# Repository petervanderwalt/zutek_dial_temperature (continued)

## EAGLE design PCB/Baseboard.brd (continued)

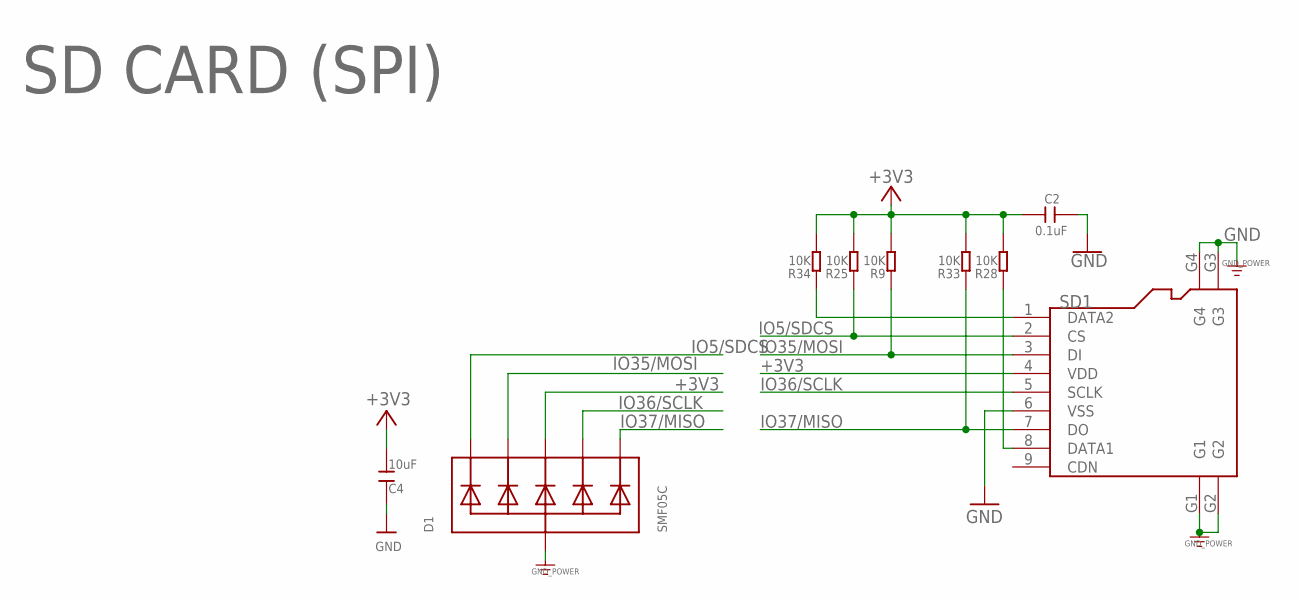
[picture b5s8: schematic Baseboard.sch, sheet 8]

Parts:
C2: 0.1uF; DISCRETE_C0603
C4: 10uF; DISCRETE_C1206
D1: SMF05C; SOT363
R9, R25, R28, R33, R34: 10K; DISCRETE_R0603
SD1: HOLDER-MICROSD-9P; 9P-SMD-W/-RING

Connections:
+3V3: C2.2, C4.2, D1.4 (C3), R9.2, R25.2, R28.2, R33.2, R34.2, SD1.4 (VDD); also elsewhere on the board
GND: C2.1, C4.1, D1.2 (A), SD1.6 (VSS), SD1.G1, SD1.G2, SD1.G3, SD1.G4; also elsewhere on the board
IO5/SDCS: D1.1 (C1), R25.1, SD1.2 (CS); also elsewhere on the board
IO35/MOSI: D1.3 (C2), R9.1, SD1.3 (DI); also elsewhere on the board
IO36/SCLK: D1.5 (C4), SD1.5 (SCLK); also elsewhere on the board
IO37/MISO: D1.6 (C5), R33.1, SD1.7 (DO); also elsewhere on the board
unnamed: R34.1, SD1.1 (DATA2)
unnamed: R28.1, SD1.8 (DATA1)

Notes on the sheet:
SD CARD (SPI)

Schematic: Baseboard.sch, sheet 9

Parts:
C28, C29: 22P; C0603
C30, C31, C34: 0.1uF; C0603
C32, C35: 10uF; C1206
C33: 0.47uF; C0603
IC2: CH376; CH376S-SOIC
R46, R61: 100K; R0603
USB1: USB-A-H
XTAL2: 12MHz; CRYSTAL_3.2X2.5

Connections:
+3V3: C30.2, C33.1, C34.1, C35.1, IC2.PCS#, IC2.V3, IC2.VCC, R46.2, R61.2; also elsewhere on the board
+5V: C31.2, C32.2, USB1.VBUS; also elsewhere on the board
GND: C28.2, C29.2, C30.1, C31.1, C32.1, C34.2, C35.2, IC2.GND, IC2.RD#, IC2.WR#, USB1.GND; also elsewhere on the board
IO35/MOSI: IC2.SDI/D6; also elsewhere on the board
IO36/SCLK: IC2.SCK/D5; also elsewhere on the board
IO37/MISO: IC2.SDO/D7; also elsewhere on the board
unnamed: IC2.UD+, USB1.D+
unnamed: IC2.UD-, USB1.D-
unnamed: C28.1, IC2.XI, XTAL2.1
unnamed: C29.1, IC2.XO, XTAL2.2
unnamed: IC2.TXD, R46.1
RESET_IN: C33.2, IC2.RSTI
RESET_OUT: IC2.SD-DO
SPI_BUSY: IC2.BZ/D4
USBMS_CS: IC2.SCS/D3, R61.1; also elsewhere on the board
USB_INT: IC2.INT#; also elsewhere on the board

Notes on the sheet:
USB MASS STORAGE (SPI)

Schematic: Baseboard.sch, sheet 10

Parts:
D2_M1, D2_M2, D2_M3, D2_M4, D2_M5, D2_M6, D2_M7, D2_M8: GRN; CHIP-LED0603
D30_RL1, D30_RL2, D30_RL3, D30_RL4, D30_RL5, D30_RL6, D30_RL7, D30_RL8: B5819W; SOD123FL
F1_RL1, F1_RL2, F1_RL3, F1_RL4, F1_RL5, F1_RL6, F1_RL7, F1_RL8: 24V 460mA; 1206L
IC7: PCF8574T; SO16W
MOSFET1, MOSFET2, MOSFET3, MOSFET4, MOSFET5, MOSFET6, MOSFET7, MOSFET8: WJ212R-THR-3.5-2
Q2_RL1, Q2_RL2, Q2_RL3, Q2_RL4, Q2_RL5, Q2_RL6, Q2_RL7, Q2_RL8: ST3422A; SOT-23
R1, R3, R6, R62, R84, R85, R86, R87, R88, R90, R92, R94, R100, R101, R102, R103: 1K; R0603
R2, R4, R8, R63, R89, R91, R93, R95: 100K; R0603
R47, R48, R49, R50, R82, R83, R96, R97, R98, R99: 10K; R0603
SJ8, SJ9, SJ10: SJ

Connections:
+3V3: IC7.16 (VDD), R82.2, R83.2, R84.1, R85.1, R86.1, R87.1, R100.1, R101.1, R102.1, R103.1; also elsewhere on the board
+24V: D30_RL1.C, D30_RL2.C, D30_RL3.C, D30_RL4.C, D30_RL5.C, D30_RL6.C, D30_RL7.C, D30_RL8.C, F1_RL1.2, F1_RL2.2, F1_RL3.2, F1_RL4.2, F1_RL5.2, F1_RL6.2, F1_RL7.2, F1_RL8.2, R47.1, R48.1, R49.1, R50.1, R96.1, R97.1, R98.1, R99.1; also elsewhere on the board
GND: IC7.8 (VSS), Q2_RL1.P2 (S), Q2_RL2.P2 (S), Q2_RL3.P2 (S), Q2_RL4.P2 (S), Q2_RL5.P2 (S), Q2_RL6.P2 (S), Q2_RL7.P2 (S), Q2_RL8.P2 (S), R2.1, R4.1, R8.1, R63.1, R89.1, R91.1, R93.1, R95.1, SJ8.1, SJ9.1, SJ10.1; also elsewhere on the board
INTERRUPT_OPTOIN: IC7.13 (!INT); also elsewhere on the board
IO3/TWI_SDA: IC7.15 (SDA), R82.1; also elsewhere on the board
IO4/TWI_SCK: IC7.14 (SCL), R83.1; also elsewhere on the board
MOSFET1: IC7.4 (P0), R62.1
MOSFET1-GND: D30_RL2.A, MOSFET1.2A, MOSFET1.2B, Q2_RL2.P3 (D), R47.2
MOSFET2: IC7.5 (P1), R3.1
MOSFET2-GND: D30_RL3.A, MOSFET2.2A, MOSFET2.2B, Q2_RL3.P3 (D), R48.2
MOSFET3: IC7.6 (P2), R1.1
MOSFET3-GND: D30_RL4.A, MOSFET3.2A, MOSFET3.2B, Q2_RL4.P3 (D), R49.2
MOSFET4: IC7.7 (P3), R6.1
MOSFET4-GND: D30_RL5.A, MOSFET4.2A, MOSFET4.2B, Q2_RL5.P3 (D), R50.2
MOSFET5: IC7.9 (P4), R88.1
MOSFET5-GND: D30_RL1.A, MOSFET5.2A, MOSFET5.2B, Q2_RL1.P3 (D), R96.2
MOSFET6: IC7.10 (P5), R90.1
MOSFET6-GND: D30_RL6.A, MOSFET6.2A, MOSFET6.2B, Q2_RL6.P3 (D), R97.2
MOSFET7: IC7.11 (P6), R92.1
MOSFET7-GND: D30_RL7.A, MOSFET7.2A, MOSFET7.2B, Q2_RL7.P3 (D), R98.2
MOSFET8: IC7.12 (P7), R94.1
MOSFET8-GND: D30_RL8.A, MOSFET8.2A, MOSFET8.2B, Q2_RL8.P3 (D), R99.2
unnamed: D2_M3.C, Q2_RL4.P1 (G), R1.2, R2.2
unnamed: D2_M2.C, Q2_RL3.P1 (G), R3.2, R4.2
unnamed: D2_M4.C, Q2_RL5.P1 (G), R6.2, R8.2
unnamed: D2_M1.C, Q2_RL2.P1 (G), R62.2, R63.2
unnamed: D2_M1.A, R84.2
unnamed: F1_RL3.1, MOSFET2.1A, MOSFET2.1B
unnamed: F1_RL2.1, MOSFET3.1A, MOSFET3.1B
unnamed: F1_RL1.1, MOSFET4.1A, MOSFET4.1B
unnamed: IC7.1 (A0), SJ8.2
unnamed: IC7.2 (A1), SJ9.2
unnamed: IC7.3 (A2), SJ10.2
unnamed: D2_M5.C, Q2_RL1.P1 (G), R88.2, R89.2
unnamed: D2_M2.A, R85.2
unnamed: D2_M3.A, R86.2
unnamed: D2_M4.A, R87.2
unnamed: F1_RL4.1, MOSFET1.1A, MOSFET1.1B
unnamed: D2_M6.C, Q2_RL6.P1 (G), R90.2, R91.2
unnamed: D2_M7.C, Q2_RL7.P1 (G), R92.2, R93.2
unnamed: D2_M8.C, Q2_RL8.P1 (G), R94.2, R95.2
unnamed: F1_RL7.1, MOSFET6.1A, MOSFET6.1B
unnamed: F1_RL6.1, MOSFET7.1A, MOSFET7.1B
unnamed: F1_RL5.1, MOSFET8.1A, MOSFET8.1B
unnamed: D2_M6.A, R100.2
unnamed: D2_M7.A, R101.2
unnamed: D2_M8.A, R102.2
unnamed: F1_RL8.1, MOSFET5.1A, MOSFET5.1B
unnamed: D2_M5.A, R103.2

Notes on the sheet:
MOSFET OUTPUTS (GPIO)

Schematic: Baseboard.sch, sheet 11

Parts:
C107_N0, C107_N1, C107_N2, C107_N3, C107_N4, C107_N5, C107_N6, C107_N7: 100nF; C0402
D2_I1, D2_I2, D2_I3, D2_I4, D2_I5, D2_I6, D2_I7, D2_I8: GRN; CHIP-LED0603
IC6: PCF8574T; SO16W
INPUT1, INPUT2, INPUT3, INPUT4, INPUT5, INPUT6, INPUT7, INPUT8: WJ212R-THR-3.5-2
R21, R23, R55, R56, R78, R79, R80, R81, R104, R105, R106, R107, R108, R109, R110, R111: 1K; R0603
R76, R77: 10K; R0603
R124_N0, R124_N1, R124_N2, R124_N3, R124_N4, R124_N5, R124_N6, R124_N7: 510R; R0402
SJ5, SJ6, SJ7: SJ
U34_N0, U34_N1, U34_N2, U34_N3, U34_N4, U34_N5, U34_N6, U34_N7: EL357N-G; OPTO_EL357N-G

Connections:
+3V3: IC6.16 (VDD), R21.1, R23.1, R55.1, R56.1, R76.2, R77.2, R78.1, R79.1, R80.1, R81.1, R104.1, R105.1, R106.1, R107.1, R108.1, R109.1, R110.1, R111.1; also elsewhere on the board
GND: C107_N0.2, C107_N1.2, C107_N2.2, C107_N3.2, C107_N4.2, C107_N5.2, C107_N6.2, C107_N7.2, IC6.8 (VSS), SJ5.1, SJ6.1, SJ7.1, U34_N0.3 (ET), U34_N1.3 (ET), U34_N2.3 (ET), U34_N3.3 (ET), U34_N4.3 (ET), U34_N5.3 (ET), U34_N6.3 (ET), U34_N7.3 (ET); also elsewhere on the board
INTERRUPT_OPTOIN: IC6.13 (!INT); also elsewhere on the board
IO3/TWI_SDA: IC6.15 (SDA), R76.1; also elsewhere on the board
IO4/TWI_SCK: IC6.14 (SCL), R77.1; also elsewhere on the board
unnamed: R124_N1.1, U34_N1.1 (A)
unnamed: R124_N2.1, U34_N2.1 (A)
unnamed: R124_N3.1, U34_N3.1 (A)
unnamed: INPUT1.2A, INPUT1.2B, R124_N0.2
unnamed: INPUT2.2A, INPUT2.2B, R124_N1.2
unnamed: INPUT3.2A, INPUT3.2B, R124_N2.2
unnamed: INPUT4.2A, INPUT4.2B, R124_N3.2
unnamed: IC6.1 (A0), SJ5.2
unnamed: IC6.2 (A1), SJ6.2
unnamed: IC6.3 (A2), SJ7.2
unnamed: R124_N4.1, U34_N4.1 (A)
unnamed: R124_N5.1, U34_N5.1 (A)
unnamed: R124_N6.1, U34_N6.1 (A)
unnamed: R124_N7.1, U34_N7.1 (A)
unnamed: INPUT5.2A, INPUT5.2B, R124_N4.2
unnamed: INPUT6.2A, INPUT6.2B, R124_N5.2
unnamed: R124_N0.1, U34_N0.1 (A)
unnamed: INPUT7.2A, INPUT7.2B, R124_N6.2
unnamed: INPUT8.2A, INPUT8.2B, R124_N7.2
unnamed: D2_I1.A, R104.2
unnamed: D2_I2.A, R105.2
unnamed: D2_I3.A, R106.2
unnamed: D2_I4.A, R107.2
unnamed: D2_I5.A, R108.2
unnamed: D2_I6.A, R109.2
unnamed: D2_I7.A, R110.2
unnamed: D2_I8.A, R111.2
unnamed: INPUT8.1A, INPUT8.1B, U34_N7.2 (C)
unnamed: INPUT7.1A, INPUT7.1B, U34_N6.2 (C)
unnamed: INPUT6.1A, INPUT6.1B, U34_N5.2 (C)
unnamed: INPUT5.1A, INPUT5.1B, U34_N4.2 (C)
unnamed: INPUT4.1A, INPUT4.1B, U34_N3.2 (C)
unnamed: INPUT3.1A, INPUT3.1B, U34_N2.2 (C)
unnamed: INPUT2.1A, INPUT2.1B, U34_N1.2 (C)
unnamed: INPUT1.1A, INPUT1.1B, U34_N0.2 (C)
OPTO1: C107_N0.1, D2_I1.C, IC6.4 (P0), R21.2, U34_N0.4 (CT)
OPTO2: C107_N1.1, D2_I2.C, IC6.5 (P1), R23.2, U34_N1.4 (CT)
OPTO3: C107_N2.1, D2_I3.C, IC6.6 (P2), R55.2, U34_N2.4 (CT)
OPTO4: C107_N3.1, D2_I4.C, IC6.7 (P3), R56.2, U34_N3.4 (CT)
OPTO5: C107_N4.1, D2_I5.C, IC6.9 (P4), R78.2, U34_N4.4 (CT)
OPTO6: C107_N5.1, D2_I6.C, IC6.10 (P5), R79.2, U34_N5.4 (CT)
OPTO7: C107_N6.1, D2_I7.C, IC6.11 (P6), R80.2, U34_N6.4 (CT)
OPTO8: C107_N7.1, D2_I8.C, IC6.12 (P7), R81.2, U34_N7.4 (CT)

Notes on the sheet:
OPTO INPUTS (GPIO)

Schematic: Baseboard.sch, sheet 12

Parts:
D51: 1N4148; SOD-323
DS18B20: WJ212R-THR-3.5-3
Q34: BC849SMD; SOT23-BEC
R57: 4K7; R0603
R154: 1K; R0603
R155: 100K; R0603
RELAY: WJ212R-THR-3.5-3
U$12: JRC-21F-4100

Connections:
5V: DS18B20.1A, DS18B20.1B, R57.2; also elsewhere on the board
5V_BOTTOM: D51.C, U$12.COIL-
COIL-1: D51.A, Q34.C, U$12.COIL+ (COIL=)
DS18B20: DS18B20.2A, DS18B20.2B, R57.1; also elsewhere on the board
GND: DS18B20.3A, DS18B20.3B; also elsewhere on the board
GND_BOTTOM: Q34.E, R155.2
unnamed: Q34.B, R154.1, R155.1
RELAY1: R154.2; also elsewhere on the board
RELAY-C: RELAY.3A, RELAY.3B, U$12.C1 (C), U$12.C2 (C)
RELAY-NC: RELAY.2A, RELAY.2B, U$12.NC
RELAY-NO: RELAY.1A, RELAY.1B, U$12.NO

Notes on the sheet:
MECHANICAL RELAY (GPIO)
ONEWIRE DS18B20 (GPIO)

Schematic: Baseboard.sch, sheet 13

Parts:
C38, C42, C43, C44, C45, C46, C47: 0.1uF; 0603
C39, C40: 10pF; 0603
C41, C48: 10uF; 0603
C49, C52: 10nF; 0603
C50: 4.7uF; 0603
C51: 1nF; 1206
C53, C54: 6.8nF; 0603
C55: 22nF; 0603
D25: DT1042-04SO; SOT-23-6
FB2: 470Ω; 0603
J2: MAGJACK-POE; MAGJACK-SYM_LED
R17: 1M; 0603
R18, R58: 1k; 0603
R59: 12.4k; 0603
R60, R64, R65, R75: 10k; 0603
R66, R71, R72, R73: 49.9; 0603
R67, R68, R69, R70: 33; 0603
R74: 10; 0603
U6: W5500; LQFP-48
Y1: 25MHz; CRYSTAL-SMD-2.0X1.6MM

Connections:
3.3V: C38.1, C41.1, FB2.1, R18.2, R58.2, R60.2, R64.2, R65.2, U6.28 (VDD); also elsewhere on the board
ACT_LED: J2.14 (GRN-), U6.27 (ACTLED)
ETH_!CS!: U6.32 (!CS!)
ETH_!INT!: U6.36 (!INT!)
ETH_!RST!: U6.37 (!RST!)
GND: C38.2, C39.2, C40.2, C41.2, C42.2, C43.2, C44.2, C45.2, C46.2, C47.2, C48.2, C49.2, C50.2, C51.2, C52.2, C55.2, R59.1, R75.1, U6.3 (AGND), U6.9 (AGND), U6.14 (AGND), U6.16 (AGND), U6.19 (AGND), U6.29 (GND), U6.48 (AGND); also elsewhere on the board
GND-ISO: C51.1, D25.2 (VSS), J2.7 (GND), J2.8 (GND), J2.S1 (SHLD), J2.S2 (SHLD)
LINK_LED: J2.12 (YLW-), U6.25 (LINKLED)
unnamed: C39.1, R17.1, U6.31 (XO), Y1.1
unnamed: C40.1, R17.2, U6.30 (XI), Y1.3 (2)
unnamed: J2.13 (GRN+), R58.1
unnamed: J2.11 (YLW+), R18.1
unnamed: R59.2, U6.10 (EXRES1)
unnamed: C49.1, U6.22 (1V20)
unnamed: C50.1, U6.20 (TOCAP)
unnamed: R75.2, U6.23 (RSVD23)
PMODE0: R65.1, U6.45 (PMODE0)
PMODE1: R64.1, U6.44 (PMODE1)
PMODE2: R60.1, U6.43 (PMODE2)
PW+: J2.9 (PW+)
PW-: J2.10 (PW-)
RCT: C52.1, J2.5 (RCT), R66.1, R71.1
RD+: C54.2, D25.3 (IO2), J2.3 (RD+)
RD-: C53.2, D25.4 (IO3), J2.6 (RD-)
RXN: R70.1, U6.5 (RXN)
RXN1: C53.1, R70.2, R71.2
RXP: R69.1, U6.6 (RXP)
RXP1: C54.1, R66.2, R69.2
SPI_CIPO: U6.34 (MISO); also elsewhere on the board
SPI_COPI: U6.35 (MOSI); also elsewhere on the board
SPI_SCK: U6.33 (SCK); also elsewhere on the board
TCT: C55.1, J2.4 (TCT), R74.1
TD+: D25.1 (IO1), J2.1 (TD+), R67.2, R72.1
TD-: D25.6 (IO4), J2.2 (TD-), R68.2, R73.1
TXN: R68.1, U6.1 (TXN)
TXP: R67.1, U6.2 (TXP)
VCCA: C42.1, C43.1, C44.1, C45.1, C46.1, C47.1, C48.1, FB2.2, R72.2, R73.2, R74.2, U6.4 (AVDD), U6.8 (AVDD), U6.11 (AVDD), U6.15 (AVDD), U6.17 (AVDD), U6.21 (AVDD)

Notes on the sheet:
Default: PMODE 111 10/100 Auto-Negotiate
DNP
ETHERNET (SPI)

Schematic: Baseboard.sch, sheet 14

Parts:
H2, H3, H4: STAND-OFF-REFLOW-M2.5_2.5MM_TALL; STAND-OFF-REFLOW-M2.5
J8, J10: MICROMOD_FUNCTION_MAIN; M.2-CONNECTOR-E-FUNCTION-STANDARD

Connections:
3.3V: J8.73 (3.3V), J10.36 (EEPROM_A0), J10.73 (3.3V); also elsewhere on the board
!BOOT!: J8.66 (DFU_!BOOT!), J10.66 (DFU_!BOOT!)
!CS0!-PROCESSOR: J8.49 (F1/!CS!)
!CS1!-PROC-JUMPER: J10.49 (F1/!CS!)
!DFU-FC0!: J8.10 (DFU_!ACTIVE!)
!DFU-FC1!: J10.10 (DFU_!ACTIVE!)
!RESET!: J8.68 (DFU_!RST!), J10.68 (DFU_!RST!)
A0-PROCESSOR: J8.38 (A0)
A1-PROCESSOR/!CS1!-ALT: J10.38 (A0)
CTS1-PROCESSOR: J8.16 (FUNC_RTS)
D0-PROCESSOR: J8.47 (F0/!INT!)
D1-PROCESSOR: J10.47 (F0/!INT!)
G0-PROCESSOR: J8.53 (F3)
G1-PROCESSOR: J8.55 (F4)
G2-PROCESSOR: J8.57 (F5)
G3-PROCESSOR: J8.59 (F6)
G4-PROCESSOR/SD_CARD_!CS!: J8.61 (F7)
G5-PROCESSOR: J10.53 (F3)
G6-PROCESSOR: J10.55 (F4)
G7-PROCESSOR: J10.57 (F5)
GND: H2.1, H3.1, H4.1, J8.1 (GND), J8.2 (GND), J8.8 (GND), J8.32 (EEPROM_A2), J8.33 (GND), J8.34 (EEPROM_A1), J8.36 (EEPROM_A0), J8.39 (GND), J8.45 (GND), J8.75 (GND), J10.1 (GND), J10.2 (GND), J10.8 (GND), J10.32 (EEPROM_A2), J10.33 (GND), J10.34 (EEPROM_A1), J10.39 (GND), J10.45 (GND), J10.75 (GND); also elsewhere on the board
HOST_D+: J8.35 (USBHOST_D+)
HOST_D-: J8.37 (USBHOST_D-)
I2C_!INT!: J8.23 (I2C_!INT!), J10.23 (I2C_!INT!)
I2C_SCL: J8.21 (I2C_SCL), J10.21 (I2C_SCL); also elsewhere on the board
I2C_SDA: J8.19 (I2C_SDA), J10.19 (I2C_SDA); also elsewhere on the board
PROCESSOR_CAN-RX: J8.43 (CAN-RX)
PROCESSOR_CAN-TX: J8.41 (CAN-TX)
PWM0-PROCESSOR: J8.51 (F2/PWM)
PWM1-PROCESSOR: J10.51 (F2/PWM)
RTS1-PROCESSOR: J8.18 (FUNC_CTS)
RX1-DFU_TX-FC0-PLEX: J8.4 (DFU_FC_TX)
RX1-DFU_TX-FC1-PLEX: J10.4 (DFU_FC_TX)
RX1-PROCESSOR-PLEX: J8.13 (FUNC_TX)
RX2-PROCESSOR: J10.13 (FUNC_TX)
SDIO_DATA1/PWR_EN1_ALT: J10.71 (PWR_EN)
SDIO_DATA2/PWR_EN0_ALT: J8.71 (PWR_EN)
SPI_PROCESSOR_SCK: J8.3 (SPI_SCK), J10.3 (SPI_SCK)
SPI_PROCESSOR_SDI: J8.7 (SPI_SDO), J10.7 (SPI_SDO)
SPI_PROCESSOR_SDO: J8.5 (SPI_SDI), J10.5 (SPI_SDI)
SPI_SCK1-PROCESSOR: J10.61 (F7)
SPI_SDO1-PROCESSOR: J10.59 (F6)
TX1-DFU_RX-FC0-PLEX: J8.6 (DFU_FC_RX)
TX1-DFU_RX-FC1-PLEX: J10.6 (DFU_FC_RX)
TX1-PROCESSOR-PLEX: J8.15 (FUNC_RX)
TX2-PROCESSOR: J10.15 (FUNC_RX)
VCC: J8.72 (VCC), J8.74 (VCC), J10.72 (VCC), J10.74 (VCC)

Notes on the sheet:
Function Board Connectors
FC0
FC1
No USB Host or CAN Bus
No Flow Control
Standoff

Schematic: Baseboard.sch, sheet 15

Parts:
J11: MICROMOD_STANDARD; M.2-CARD-E-22_FUNCTION_STANDARD

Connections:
3.3V_IN: J11.73 (3.3V)
EWP: J11.40 (EEPROM_WP)
GND: J11.1 (GND), J11.33 (GND), J11.39 (GND), J11.45 (GND), J11.75 (GND), J11.GND1 (GND), J11.GND2 (GND), J11.GND3 (GND), J11.GND4 (GND), J11.GND5 (GND), J11.GND6 (GND); also elsewhere on the board
I2C_SCL: J11.21 (I2C_SCL); also elsewhere on the board
I2C_SDA: J11.19 (I2C_SDA); also elsewhere on the board
PWR_EN: J11.71 (PWR_EN)
SPI_CIPO: J11.7 (SPI_SDO); also elsewhere on the board
SPI_COPI: J11.5 (SPI_SDI); also elsewhere on the board
SPI_SCK: J11.3 (SPI_SCK); also elsewhere on the board
VCC_IN: J11.72 (VCC), J11.74 (VCC)

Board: 2 copper layers, 339 parts (6 on the bottom side), 221 nets, no tracks yet.

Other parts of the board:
FRAME12: FRAME-LEDGERNO_FOOTPRINT; DUMMY

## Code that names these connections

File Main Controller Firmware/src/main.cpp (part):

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#define PIN_NEOPIXEL    48
#define PIN_MOSFET      8
#define PIN_SPI_MOSI    35
#define PIN_SPI_SCK     36
#define PIN_SPI_MISO    37
#define PIN_CS_PT100    1
#define PIN_CS_SD       5
#define PIN_CS_USB      6
#define PIN_INT_USB     7
#define PIN_I2C_SDA     3
#define PIN_I2C_SCL     4

// --- OBJECTS ---
Adafruit_NeoPixel strip(2, PIN_NEOPIXEL, NEO_GRB + NEO_KHZ800);
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    digitalWrite(PIN_MOSFET, LOW);
    strip.begin(); strip.show();

    SPI.begin(PIN_SPI_SCK, PIN_SPI_MISO, PIN_SPI_MOSI);
    Wire.begin(I2C_ADDR_MAINBOARD, PIN_I2C_SDA, PIN_I2C_SCL, 100000);
    Wire.onRequest(onRequest);
    Wire.onReceive(onReceive);

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
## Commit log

2025-11-10 Fix yaml
2025-11-10 Upload test
2025-11-18 Work in progress
2025-11-18 Updated defaults
2025-11-18 Fix for lowering temp
2025-11-24 Test PID
2025-12-01 Fix i2c pin allocation
2025-12-01 force byte-alignment
2025-12-01 Switch from bool -> uint8_t
2026-05-02 added missing work
2026-05-18 Moved main controller firmware from seperate repo to archive folder, deleted other repo
